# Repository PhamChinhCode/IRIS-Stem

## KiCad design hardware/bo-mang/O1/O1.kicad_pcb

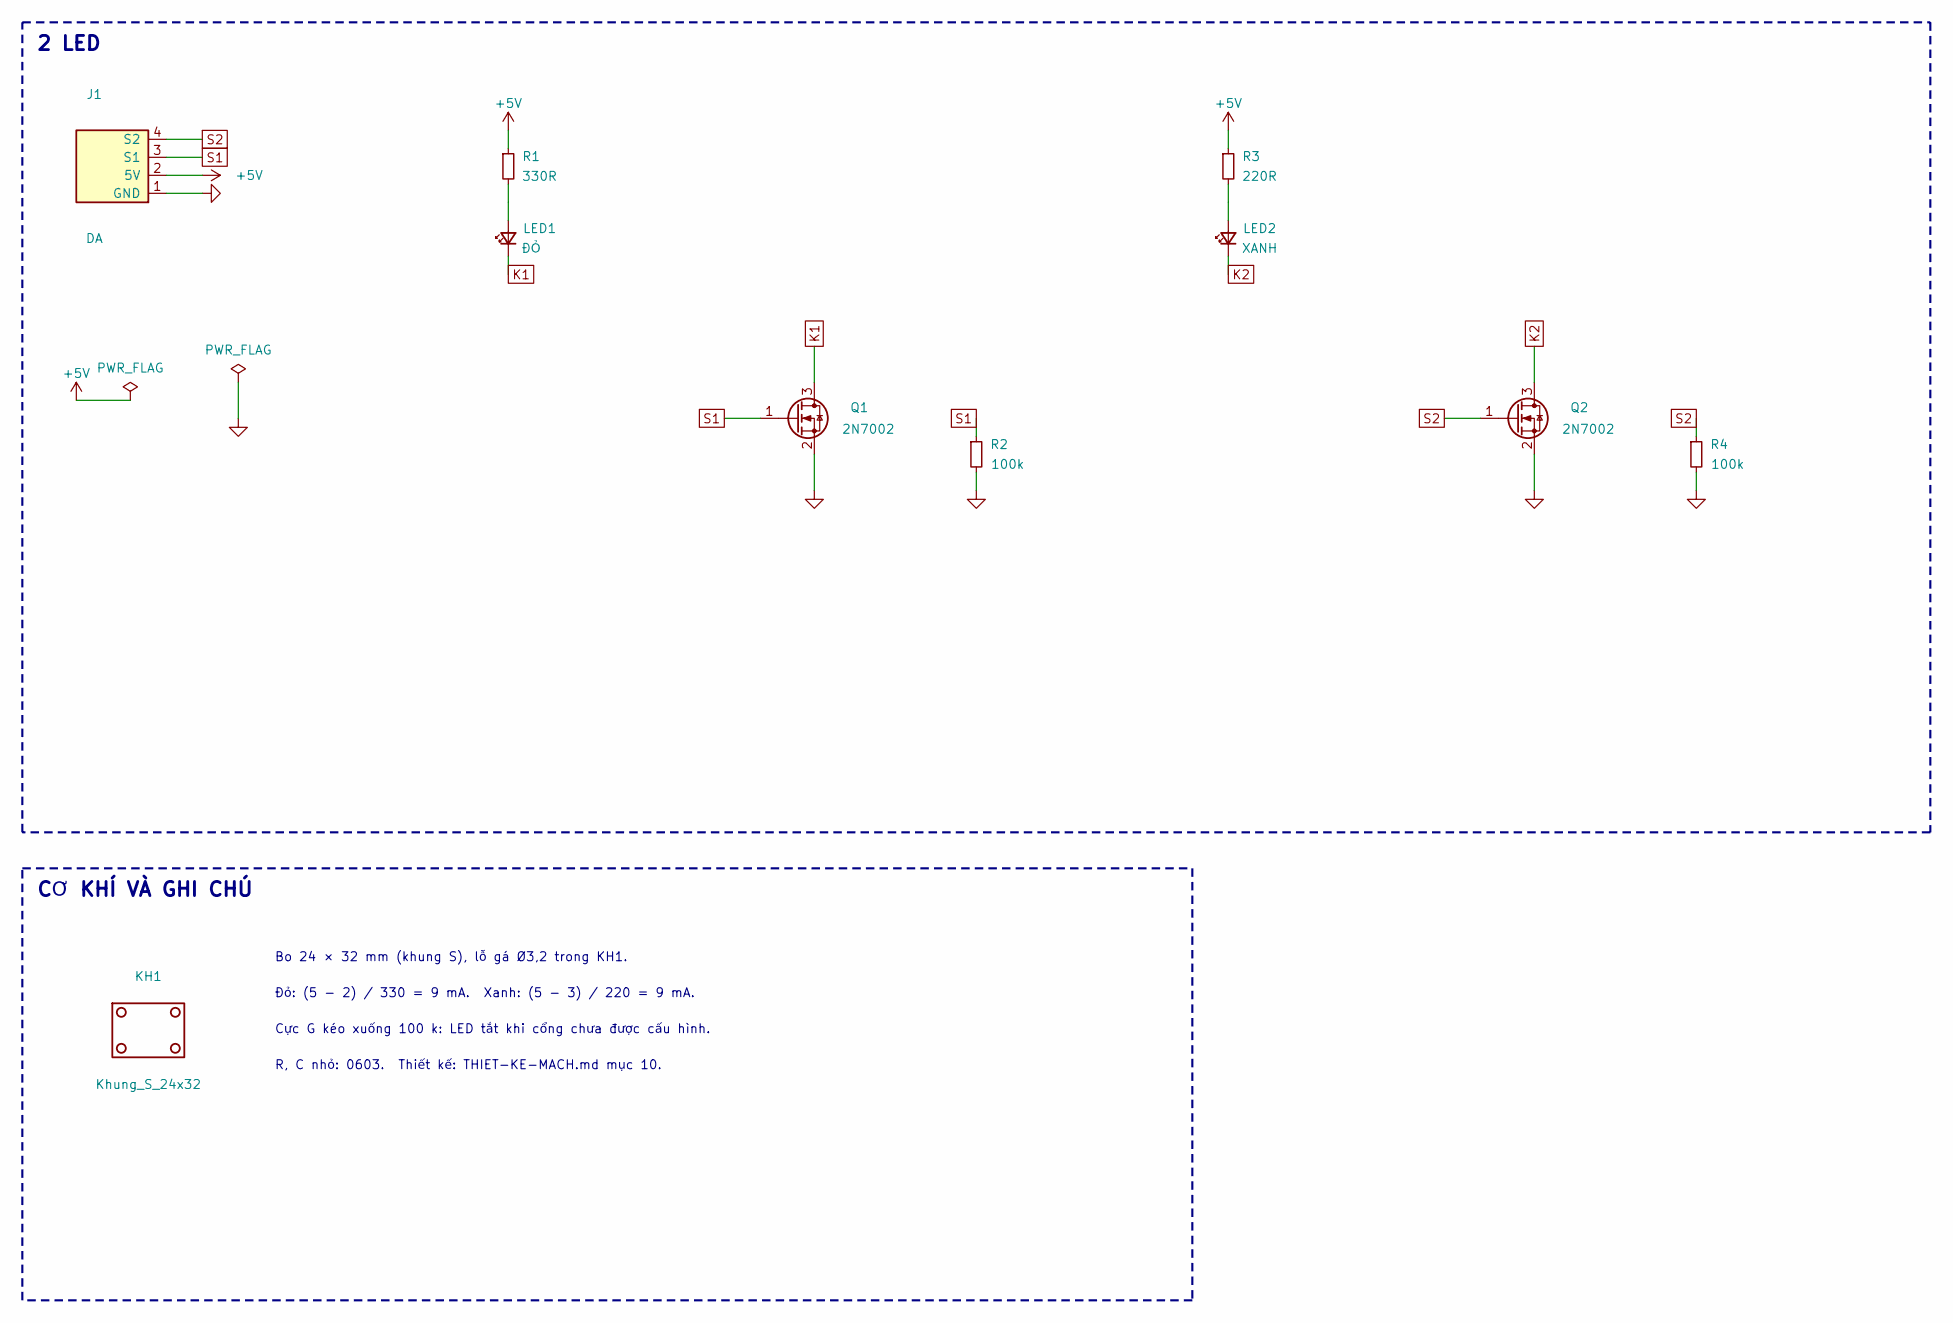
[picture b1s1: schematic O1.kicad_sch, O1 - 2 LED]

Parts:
J1: DA; Cong_PH_4P_Ngang
KH1: Khung_S_24x32
LED1: ĐỎ; LED_0603_1608Metric
LED2: XANH; LED_0603_1608Metric
Q1, Q2: 2N7002; SOT-23; MPN 2N7002
R1: 330R; R_0603_1608Metric
R2, R4: 100k; R_0603_1608Metric
R3: 220R; R_0603_1608Metric

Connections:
+5V: J1.2 (5V), R1.1, R3.1
GND: J1.1 (GND), Q1.2 (S), Q2.2 (S), R2.2, R4.2
K1: LED1.1 (K), Q1.3 (D)
K2: LED2.1 (K), Q2.3 (D)
unnamed: LED1.2 (A), R1.2
unnamed: LED2.2 (A), R3.2
S1: J1.3 (S1), Q1.1 (G), R2.1
S2: J1.4 (S2), Q2.1 (G), R4.1

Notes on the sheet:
2 LED
CƠ KHÍ VÀ GHI CHÚ
Bo 24 × 32 mm (khung S), lỗ gá Ø3,2 trong KH1.
Đỏ: (5 − 2) / 330 = 9 mA. Xanh: (5 − 3) / 220 = 9 mA.
Cực G kéo xuống 100 k: LED tắt khi cổng chưa được cấu hình.
R, C nhỏ: 0603. Thiết kế: THIET-KE-MACH.md mục 10.

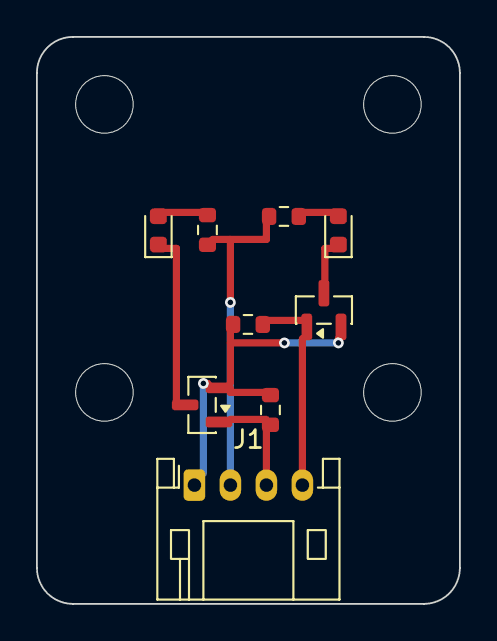
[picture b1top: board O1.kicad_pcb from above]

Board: 2 copper layers, 23.5 x 31.5 mm, 10 parts (0 on the bottom side), 8 nets.

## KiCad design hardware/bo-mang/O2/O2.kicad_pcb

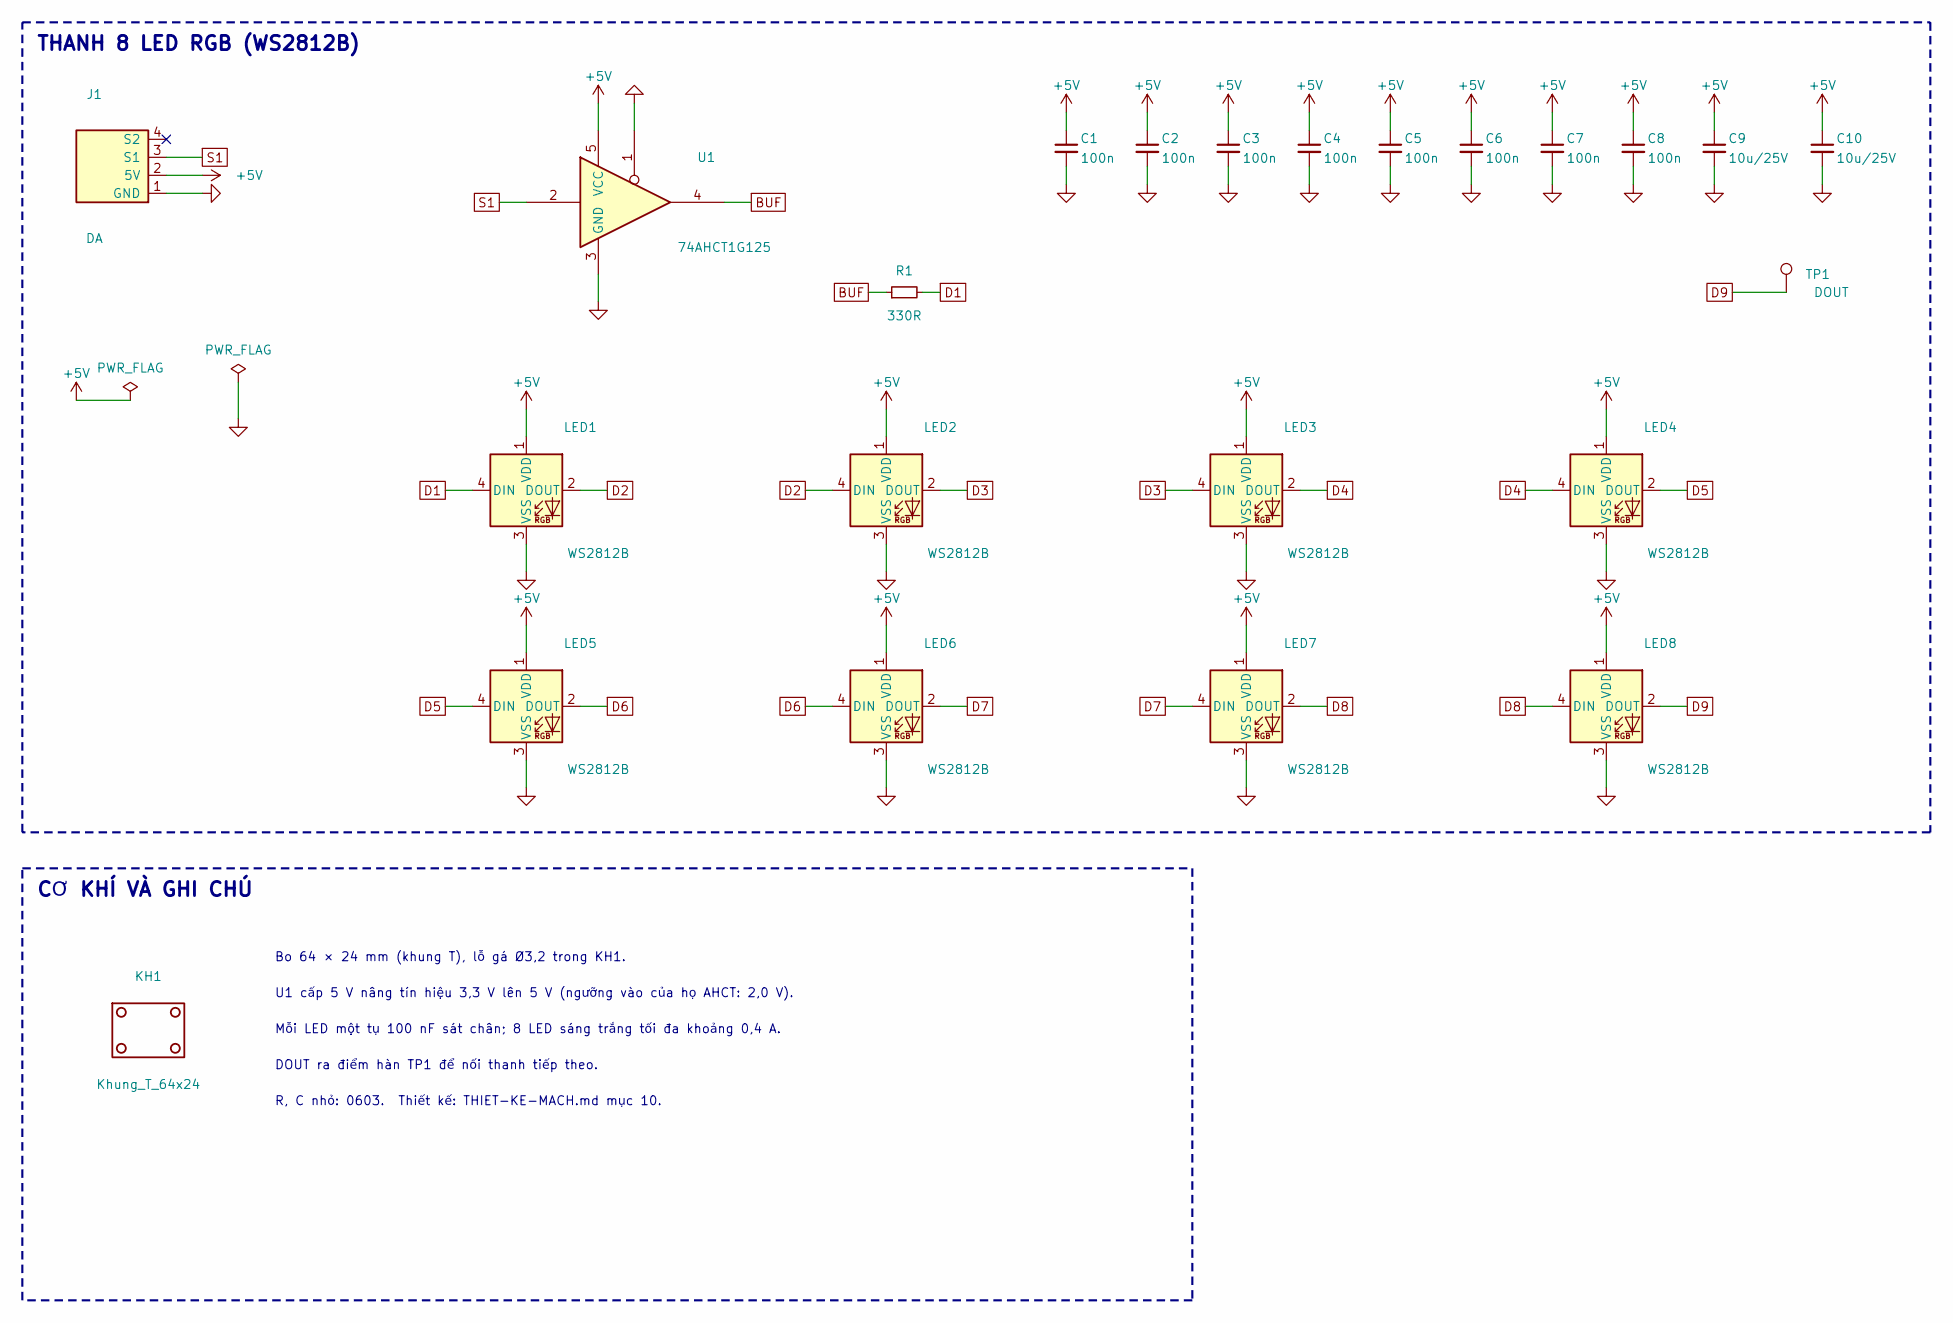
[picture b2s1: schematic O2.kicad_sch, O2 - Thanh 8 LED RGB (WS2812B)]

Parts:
C1, C2, C3, C4, C5, C6, C7, C8: 100n; C_0603_1608Metric
C9, C10: 10u/25V; C_0805_2012Metric
J1: DA; Cong_PH_4P_Ngang
KH1: Khung_T_64x24
LED1, LED2, LED3, LED4, LED5, LED6, LED7, LED8: WS2812B; LED_WS2812B_PLCC4_5.0x5.0mm_P3.2mm
R1: 330R; R_0603_1608Metric
TP1: DOUT; TestPoint_Pad_D1.5mm
U1: 74AHCT1G125; SOT-23-5; MPN SN74AHCT1G125DBVR

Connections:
+5V: C1.1, C2.1, C3.1, C4.1, C5.1, C6.1, C7.1, C8.1, C9.1, C10.1, J1.2 (5V), LED1.1 (VDD), LED2.1 (VDD), LED3.1 (VDD), LED4.1 (VDD), LED5.1 (VDD), LED6.1 (VDD), LED7.1 (VDD), LED8.1 (VDD), U1.5 (VCC)
BUF: R1.1, U1.4
D1: LED1.4 (DIN), R1.2
D2: LED1.2 (DOUT), LED2.4 (DIN)
D3: LED2.2 (DOUT), LED3.4 (DIN)
D4: LED3.2 (DOUT), LED4.4 (DIN)
D5: LED4.2 (DOUT), LED5.4 (DIN)
D6: LED5.2 (DOUT), LED6.4 (DIN)
D7: LED6.2 (DOUT), LED7.4 (DIN)
D8: LED7.2 (DOUT), LED8.4 (DIN)
D9: LED8.2 (DOUT), TP1.1
GND: C1.2, C2.2, C3.2, C4.2, C5.2, C6.2, C7.2, C8.2, C9.2, C10.2, J1.1 (GND), LED1.3 (VSS), LED2.3 (VSS), LED3.3 (VSS), LED4.3 (VSS), LED5.3 (VSS), LED6.3 (VSS), LED7.3 (VSS), LED8.3 (VSS), U1.1, U1.3 (GND)
S1: J1.3 (S1), U1.2

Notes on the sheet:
THANH 8 LED RGB (WS2812B)
CƠ KHÍ VÀ GHI CHÚ
Bo 64 × 24 mm (khung T), lỗ gá Ø3,2 trong KH1.
U1 cấp 5 V nâng tín hiệu 3,3 V lên 5 V (ngưỡng vào của họ AHCT: 2,0 V).
Mỗi LED một tụ 100 nF sát chân; 8 LED sáng trắng tối đa khoảng 0,4 A.
DOUT ra điểm hàn TP1 để nối thanh tiếp theo.
R, C nhỏ: 0603. Thiết kế: THIET-KE-MACH.md mục 10.

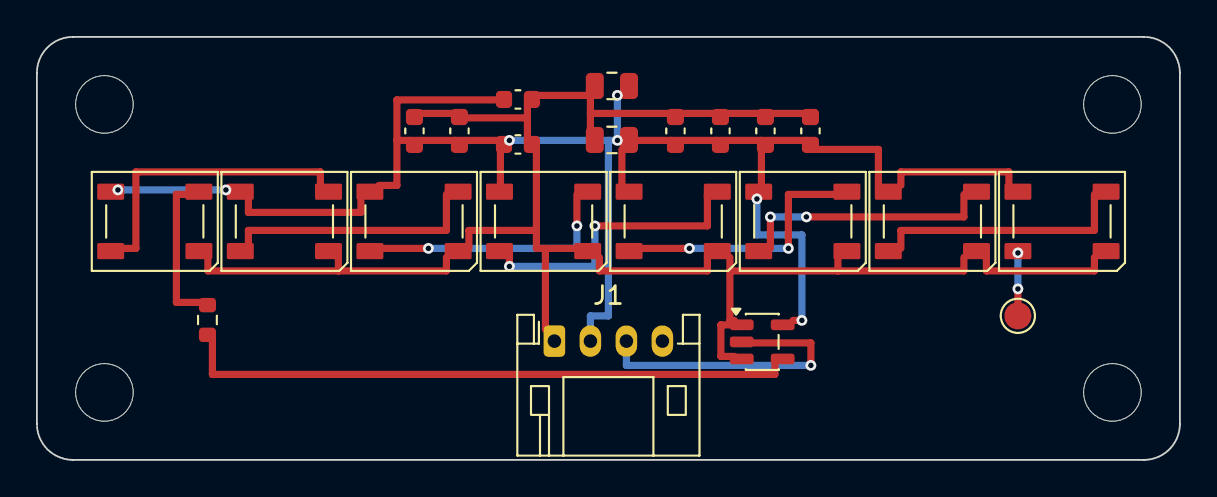
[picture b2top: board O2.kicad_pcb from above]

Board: 2 copper layers, 63.5 x 23.5 mm, 23 parts (0 on the bottom side), 13 nets.

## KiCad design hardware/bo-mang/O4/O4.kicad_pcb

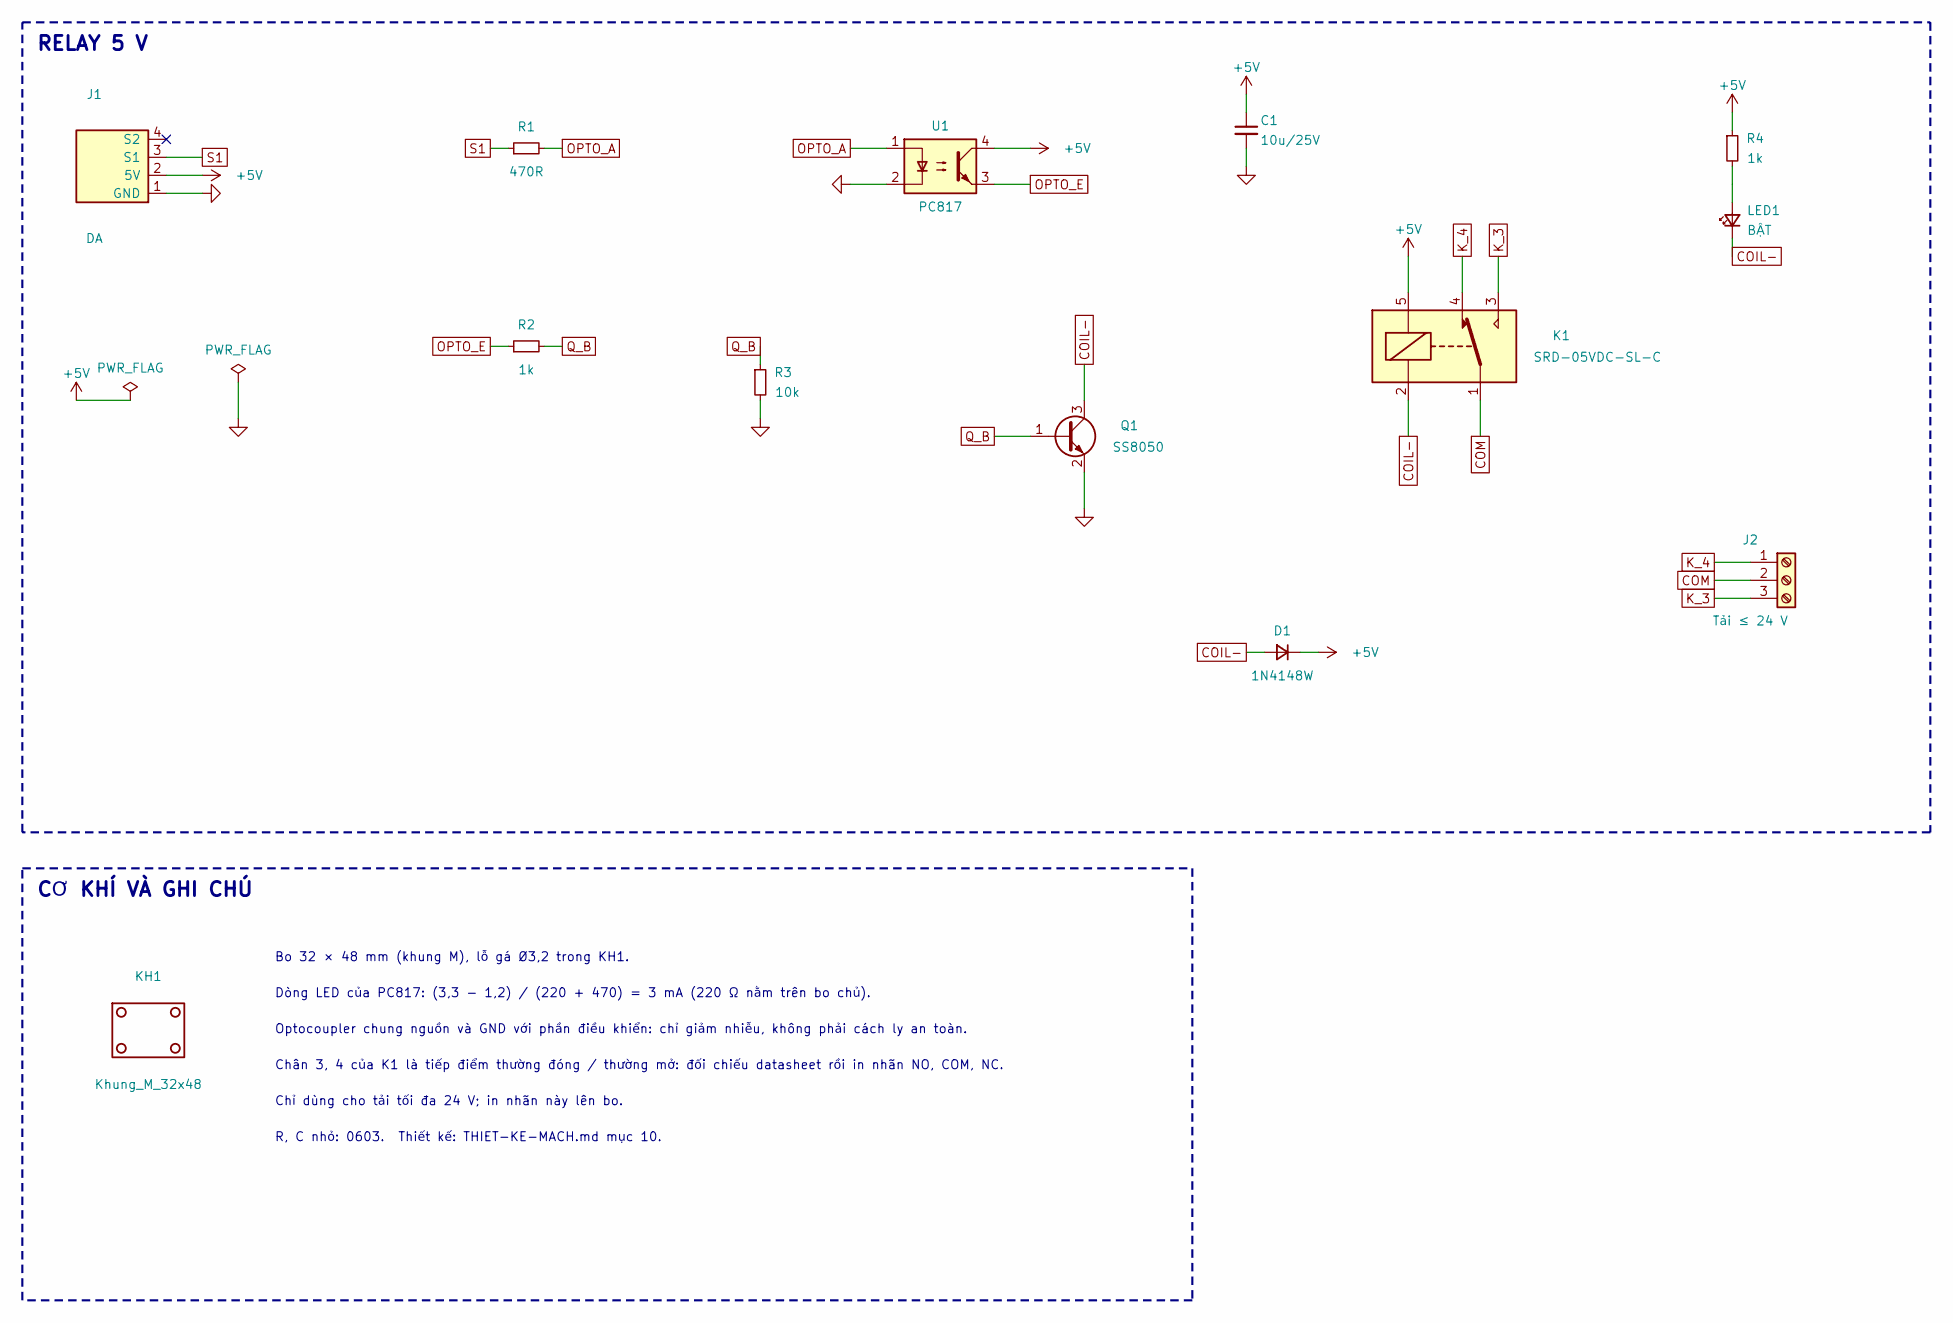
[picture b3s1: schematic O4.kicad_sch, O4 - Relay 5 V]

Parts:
C1: 10u/25V; C_0805_2012Metric
D1: 1N4148W; D_SOD-123
J1: DA; Cong_PH_4P_Ngang
J2: Tải ≤ 24 V; TerminalBlock_Phoenix_MKDS-1,5-3-5.08_1x03_P5.08mm_Horizont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
K1: SRD-05VDC-SL-C; Relay_SPDT_SANYOU_SRD_Series_Form_C
KH1: Khung_M_32x48
LED1: BẬT; LED_0603_1608Metric
Q1: SS8050; SOT-23; MPN SS8050
R1: 470R; R_0603_1608Metric
R2, R4: 1k; R_0603_1608Metric
R3: 10k; R_0603_1608Metric
U1: PC817; SMDIP-4_W9.53mm; MPN PC817

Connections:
+5V: C1.1, D1.1 (K), J1.2 (5V), K1.5, R4.1, U1.4
COIL-: D1.2 (A), K1.2, LED1.1 (K), Q1.3 (C)
COM: J2.2, K1.1
GND: C1.2, J1.1 (GND), Q1.2 (E), R3.2, U1.2
K_3: J2.3, K1.3
K_4: J2.1, K1.4
unnamed: LED1.2 (A), R4.2
OPTO_A: R1.2, U1.1
OPTO_E: R2.1, U1.3
Q_B: Q1.1 (B), R2.2, R3.1
S1: J1.3 (S1), R1.1

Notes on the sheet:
RELAY 5 V
CƠ KHÍ VÀ GHI CHÚ
Bo 32 × 48 mm (khung M), lỗ gá Ø3,2 trong KH1.
Dòng LED của PC817: (3,3 − 1,2) / (220 + 470) = 3 mA (220 Ω nằm trên bo chủ).
Optocoupler chung nguồn và GND với phần điều khiển: chỉ giảm nhiễu, không phải cách ly an toàn.
Chân 3, 4 của K1 là tiếp điểm thường đóng / thường mở: đối chiếu datasheet rồi in nhãn NO, COM, NC.
Chỉ dùng cho tải tối đa 24 V; in nhãn này lên bo.
R, C nhỏ: 0603. Thiết kế: THIET-KE-MACH.md mục 10.

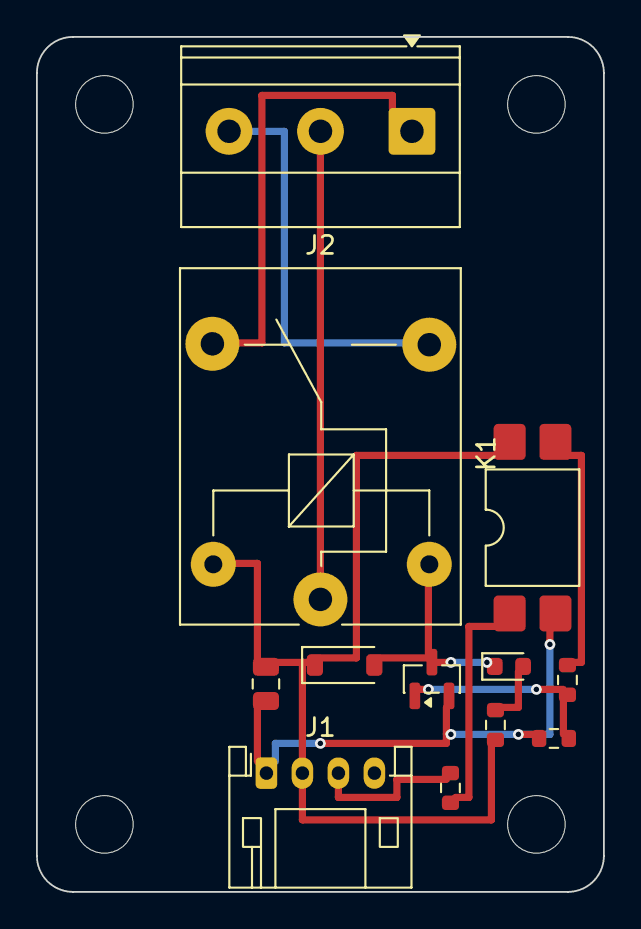
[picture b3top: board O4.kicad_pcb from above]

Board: 2 copper layers, 31.5 x 47.5 mm, 13 parts (0 on the bottom side), 11 nets.
